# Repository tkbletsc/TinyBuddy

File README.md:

TinyBuddy
=========

A host PCB for the ATtiny84 microcontroller.  Features two buttons, an activity LED, 16MHz crystal for accurate timekeeping, and USB or DC barrel jack for power.  The Rev2 design using entirely through-hole parts for easy construction.  Can be fabricated for about $7 through OSH Park.

Rev1: A micro-USB powered prototype.

- Ergonomic problem: instinct is to use it upside down
- Surface mount micro USB sucks to solder
- Programming ribbon cable presses up against reset button
- Pin silkscreens often cut off
- Labels of S7 and S8 reversed (duh!)

Rev2:

- Reoriented text and components to be used with chip facing away
- Switched to DC barrel connector for power
- Rearranged components to separate programming port, arranged things
better
- Design now uses entirely through-hole components
- Tweaked pin silk screens
- Fixed button labels

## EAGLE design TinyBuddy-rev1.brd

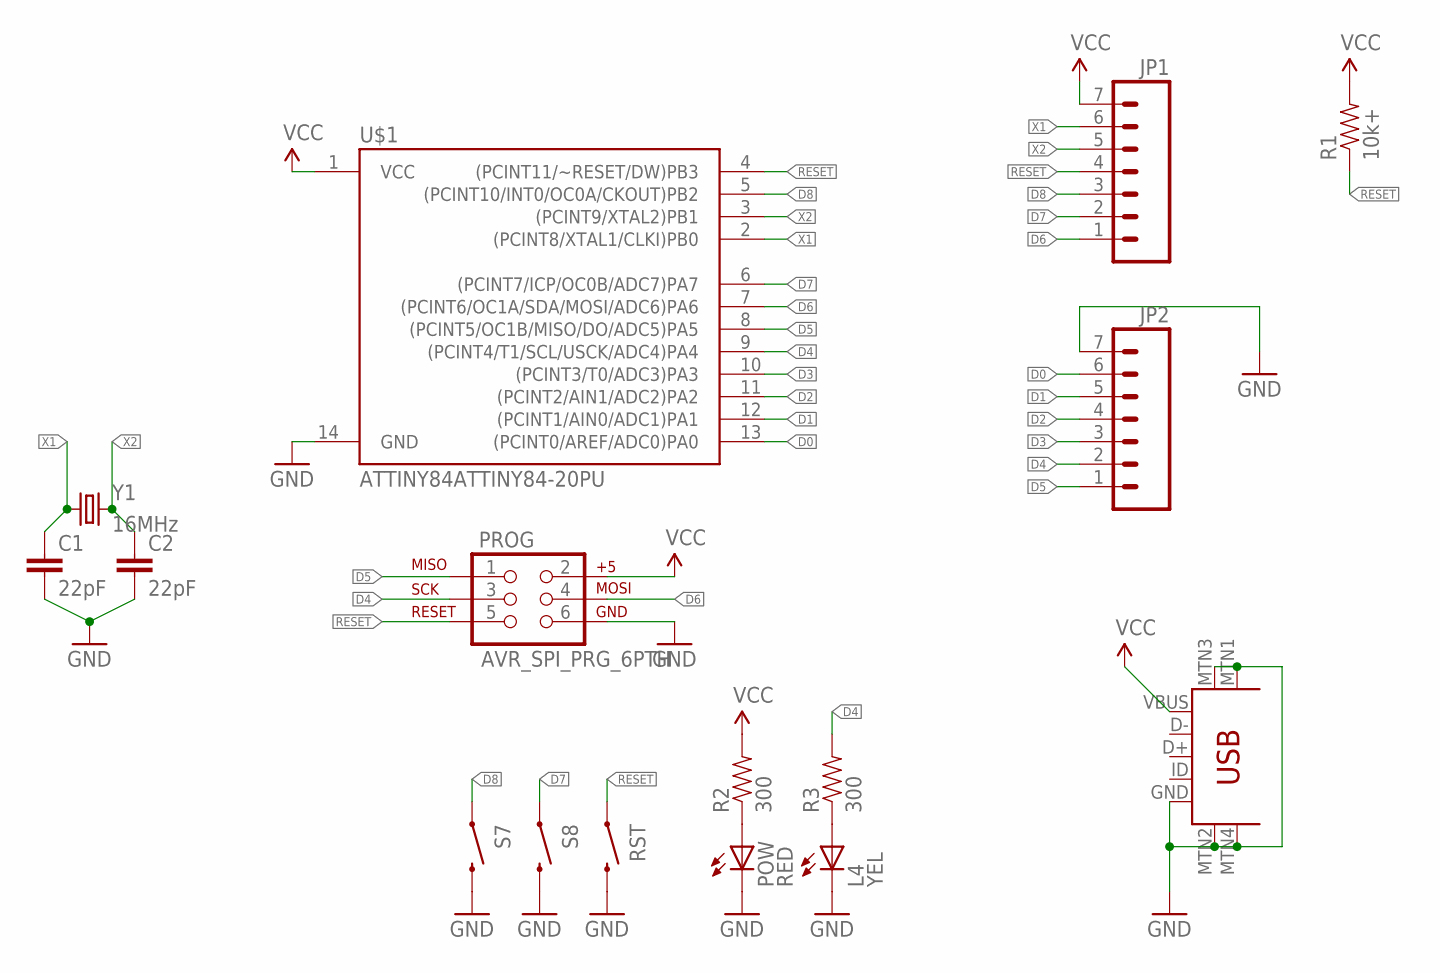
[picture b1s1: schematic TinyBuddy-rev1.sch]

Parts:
C1, C2: 22pF; CAP-PTH-SMALL
JP1, JP2: M07NOSILK; 1X07_NOSILK
L4: YEL; LED3MM
POW: RED; LED3MM
PROG: AVR_SPI_PRG_6PTH; 2X3
R1: 10k+; 1/6W-RES
R2, R3: 300; 1/6W-RES
RST: SWITCH-MOMENTARY-2PTH; TACTILE-PTH
S7, S8: SWITCH-MOMENTARY-2PTH; TACTILE-PTH
U$1: ATTINY84ATTINY84-20PU; DIL14
U$2: USB-MINIB-5PIN; USB-MINIB
Y1: 16MHz; HC49US

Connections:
D0: JP2.6, U$1.13 ((PCINT0/AREF/ADC0)PA0)
D1: JP2.5, U$1.12 ((PCINT1/AIN0/ADC1)PA1)
D2: JP2.4, U$1.11 ((PCINT2/AIN1/ADC2)PA2)
D3: JP2.3, U$1.10 ((PCINT3/T0/ADC3)PA3)
D4: JP2.2, PROG.3, R3.2, U$1.9 ((PCINT4/T1/SCL/USCK/ADC4)PA4)
D5: JP2.1, PROG.1, U$1.8 ((PCINT5/OC1B/MISO/DO/ADC5)PA5)
D6: JP1.1, PROG.4, U$1.7 ((PCINT6/OC1A/SDA/MOSI/ADC6)PA6)
D7: JP1.2, S8.1, U$1.6 ((PCINT7/ICP/OC0B/ADC7)PA7)
D8: JP1.3, S7.1, U$1.5 ((PCINT10/INT0/OC0A/CKOUT)PB2)
GND: C1.2, C2.2, JP2.7, L4.K (C), POW.K (C), PROG.6, RST.3 (2), S7.3 (2), S8.3 (2), U$1.14 (GND), U$2.GND, U$2.MTN1 (MTN2), U$2.MTN2 (MTN3), U$2.MTN3 (MTN1), U$2.MTN4
unnamed: POW.A, R2.1
unnamed: L4.A, R3.1
RESET: JP1.4, PROG.5, R1.1, RST.1, U$1.4 ((PCINT11/~RESET/DW)PB3)
VCC: JP1.7, PROG.2, R1.2, R2.2, U$1.1 (VCC), U$2.VBUS
X1: C1.1, JP1.6, U$1.2 ((PCINT8/XTAL1/CLKI)PB0), Y1.1
X2: C2.1, JP1.5, U$1.3 ((PCINT9/XTAL2)PB1), Y1.2

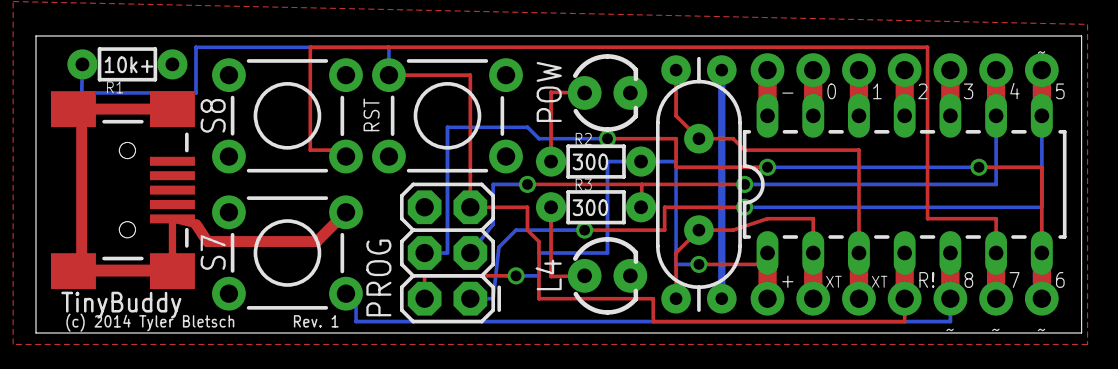
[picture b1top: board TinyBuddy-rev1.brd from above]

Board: 2 copper layers, 58.1 x 16.5 mm, 16 parts (0 on the bottom side), 16 nets.

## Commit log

2014-06-22 Initial
2014-06-22 Initial import
    Rev1: A micro-USB powered prototype.
    - Ergonomic problem: instinct is to use it upside down
    - Surface mount micro USB sucks to solder
    - Programming ribbon cable presses up against reset button
    - Pin silkscreens often cut off
    Rev2:
2014-06-22 Forgot to include rev1 brd file
2014-06-23 ignore pics

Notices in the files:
TinyBuddy-rev1.brd:
(c) 2014 Tyler Bletsch
parts and their libraries:
SparkFun-Connectors: Licensing: Creative Commons ShareAlike 4.0 International - https://creativecommons.org/licenses/by-sa/4.0
